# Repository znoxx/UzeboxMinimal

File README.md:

UzeboxMinimal
=============

Uzebox minimal design. The goal - to creat reprodusable modular design with minimal set of components.
Original project is located at http://uzebox.org

Update 16-Oct-2014 (2): Created simple MIDI expansion board. Never tested, since no MIDI devices owned :). See readme.txt inside midi subdir.
Actually project finalized.

Update 16-Oct-2014: Added video extension for AD725, same structure as in other projects (eagle,schematics,toner-transfer).
Also untested version removed.
Currently version is fully tested and confirmed working.

Update 13-Oct-2014: Added SD Card adapter.
eagle - To be opened with Eagle Cad 7.x.
schematics - Schematics, top jumpers and placement. Also an example of microSD adapter soldering. 
toner-transfer - Ready-to-print file for toner transfer. Have fun!
For best results:
Non-SDHC cards. In case using 2GB cards or bigger, create first partition about 256Mb. 
This is more, than enough for UzeBOX roms. 
Most important part partition should be FAT16 with 16K clusters.

Update 04-Oct-2014: This version is fixed somehow and soldered. Appears to be working.
Files (in mainboard dir):	
eagle - To be opened with Eagle Cad 7.x.
schematics - Schematics, top jumpers and placement
scart - connection via SCART
toner-transfer - Ready-to-print file for toner transfer. Have fun!

Update 01-Oct-2014: Current version is NOT tested in a "wild". Placed to share with forum members.
Files (not-tested dir):	
*.brd and *.sch - To be opened with Eagle Cad 7.x
schematics.pdf - Schematics
board-bottom.pdf - For toner transfer. Must be validated for correct size after/before print. Please check schematics/board layout for jumpers on top.

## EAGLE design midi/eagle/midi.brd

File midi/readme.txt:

This midi extension daughterboard was never tested in wild.
Double check schematics with F2 revision of original UzeBox at http://belogic.com/uzebox/downloads.htm before crafting.
Feel free to report any issues.

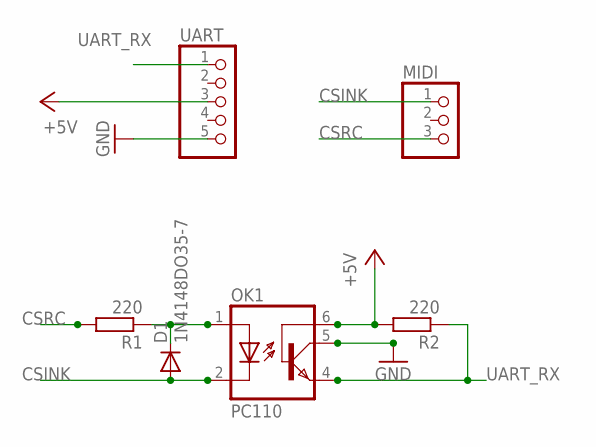
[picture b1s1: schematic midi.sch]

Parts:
D1: 1N4148DO35-7; DO35-7
MIDI: PINHD-1X3; 1X03
OK1: PC110; DIL06
R1, R2: 220; 0309V
UART: PINHD-1X5; 1X05

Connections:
+5V: OK1.6 (BAS), R2.2, UART.3
CSINK: D1.A, MIDI.1, OK1.2 (C)
CSRC: MIDI.3, R1.2
GND: OK1.5 (COL), UART.5
unnamed: D1.C, OK1.1 (A), R1.1
UART_RX: OK1.4 (EMI), R2.1, UART.1

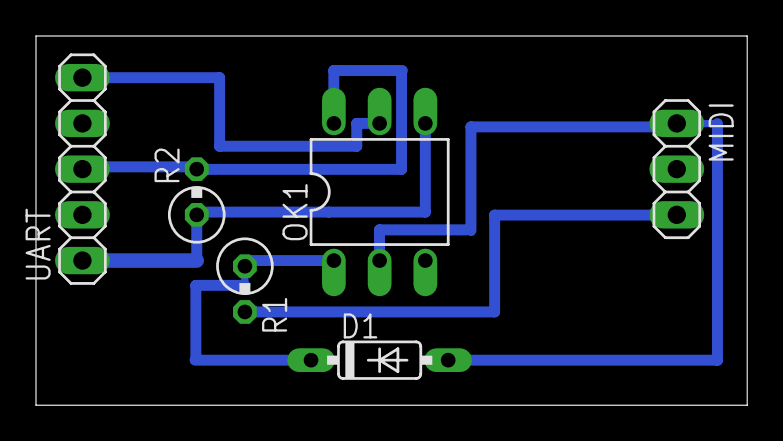
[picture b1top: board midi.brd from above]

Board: 2 copper layers, 39.5 x 20.5 mm, 6 parts (0 on the bottom side), 6 nets.

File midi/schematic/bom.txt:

Part	Value	Type
D1	1N4148	Diode DO35-7
"R1,R2"	220 Ohm	Resistor 0.125w
OK1	PC110	Optocoupler DIL06
UART 	x10 male pinhead	2.54 mm
MIDI	"x3 male pinhead, central connector cut"	2.54 mm

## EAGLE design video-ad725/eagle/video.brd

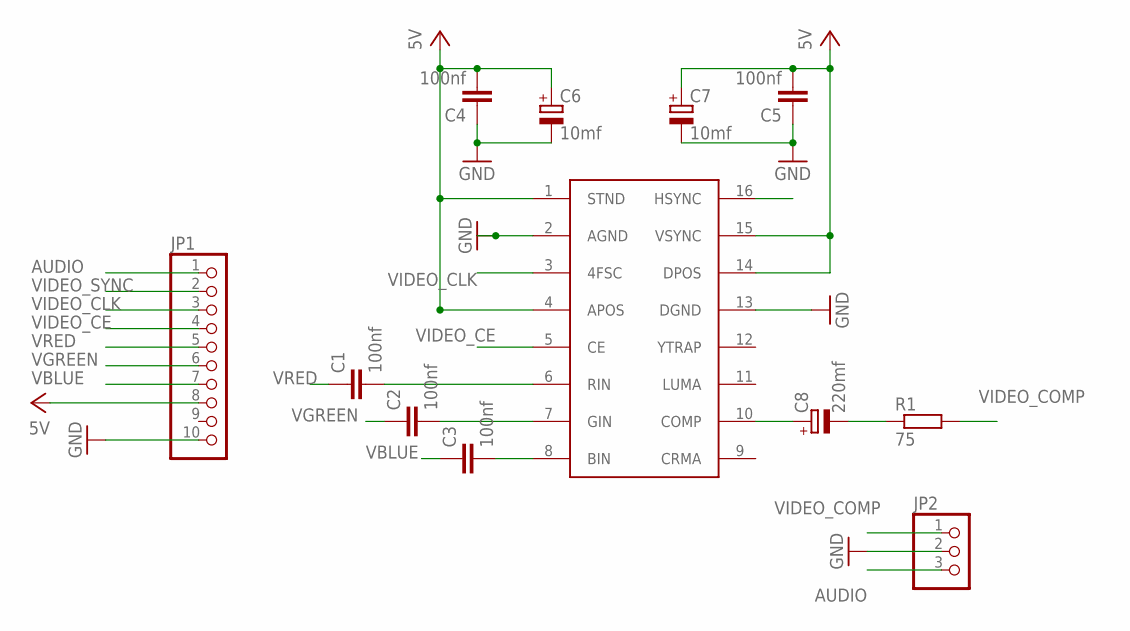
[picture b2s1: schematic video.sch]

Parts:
C1, C2, C3, C4, C5: 100nf; C0805
C6, C7: 10mf; E1,8-4
C8: 220mf; E1,8-4
JP1: PINHD-1X10; 1X10
JP2: PINHD-1X3; 1X03
R1: 75; R0805
U$1: AD725; SO16W

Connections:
AUDIO: JP1.1, JP2.3
GND: C4.1, C5.1, C6.-, C7.-, JP1.10, JP2.2, U$1.2 (AGND), U$1.13 (DGND)
unnamed: C1.2, U$1.6 (RIN)
unnamed: C2.2, U$1.7 (GIN)
unnamed: C3.2, U$1.8 (BIN)
unnamed: C8.+, U$1.10 (COMP)
unnamed: C8.-, R1.1
VBLUE: C3.1, JP1.7
VCC: C4.2, C5.2, C6.+, C7.+, JP1.8, U$1.1 (STND), U$1.4 (APOS), U$1.14 (DPOS), U$1.15 (VSYNC)
VGREEN: C2.1, JP1.6
VIDEO_CE: JP1.4, U$1.5 (CE)
VIDEO_CLK: JP1.3, U$1.3 (4FSC)
VIDEO_COMP: JP2.1, R1.2
VIDEO_SYNC: JP1.2, U$1.16 (HSYNC)
VRED: C1.1, JP1.5

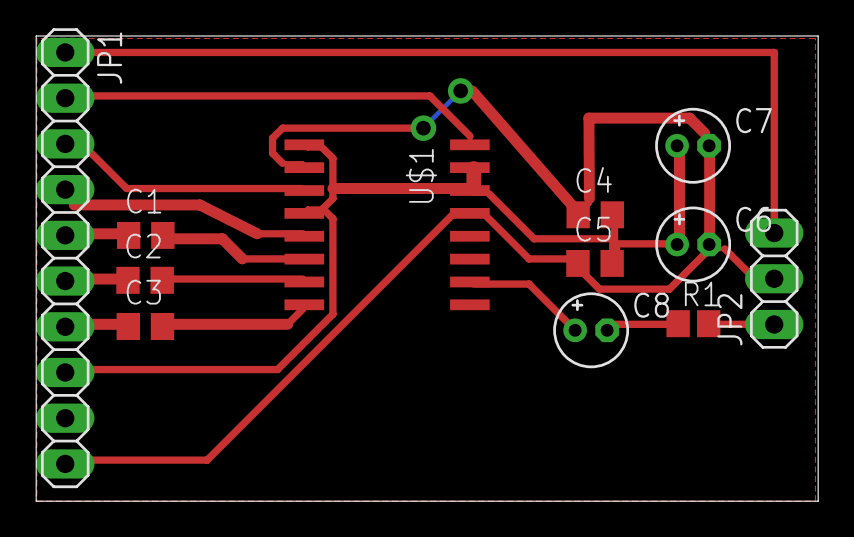
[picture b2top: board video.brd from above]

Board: 2 copper layers, 43.4 x 25.8 mm, 12 parts (0 on the bottom side), 15 nets.

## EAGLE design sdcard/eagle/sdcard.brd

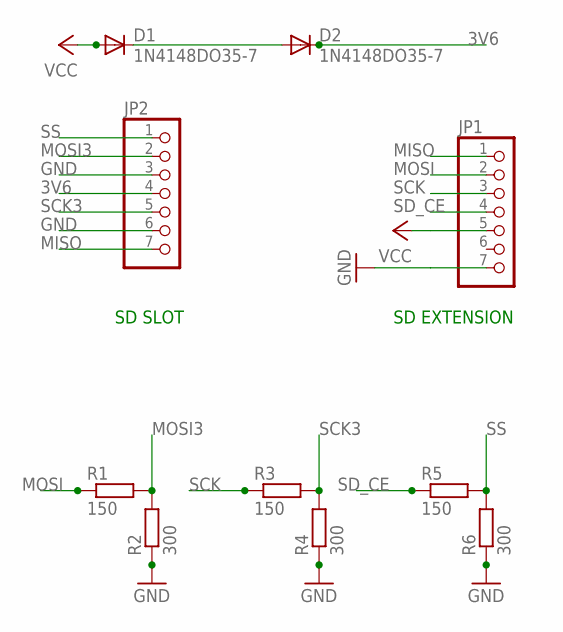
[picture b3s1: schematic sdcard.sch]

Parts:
D1, D2: 1N4148DO35-7; DO35-7
JP1, JP2: PINHD-1X7; 1X07
R1, R3, R5: 150; R0805
R2, R4, R6: 300; R0805

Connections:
3V6: D2.C, JP2.4
GND: JP1.7, JP2.3, JP2.6, R2.1, R4.1, R6.1
MISO: JP1.1, JP2.7
MOSI: JP1.2, R1.1
MOSI3: JP2.2, R1.2, R2.2
unnamed: D1.C, D2.A
SCK: JP1.3, R3.1
SCK3: JP2.5, R3.2, R4.2
SD_CE: JP1.4, R5.1
SS: JP2.1, R5.2, R6.2
VCC: D1.A, JP1.5

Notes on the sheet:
SD EXTENSION
SD SLOT

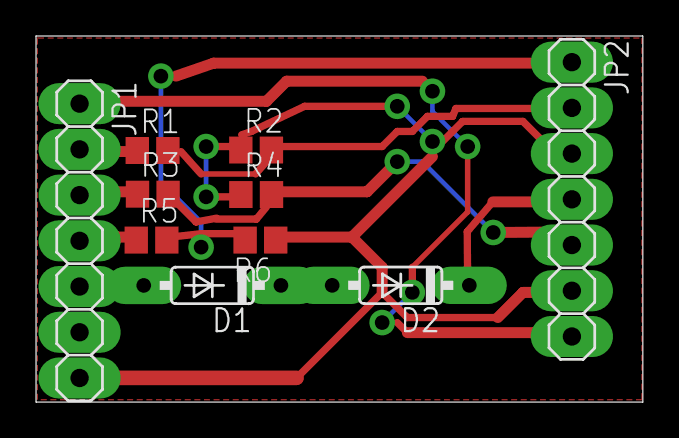
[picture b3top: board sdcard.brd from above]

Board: 2 copper layers, 33.7 x 20.3 mm, 10 parts (0 on the bottom side), 11 nets.

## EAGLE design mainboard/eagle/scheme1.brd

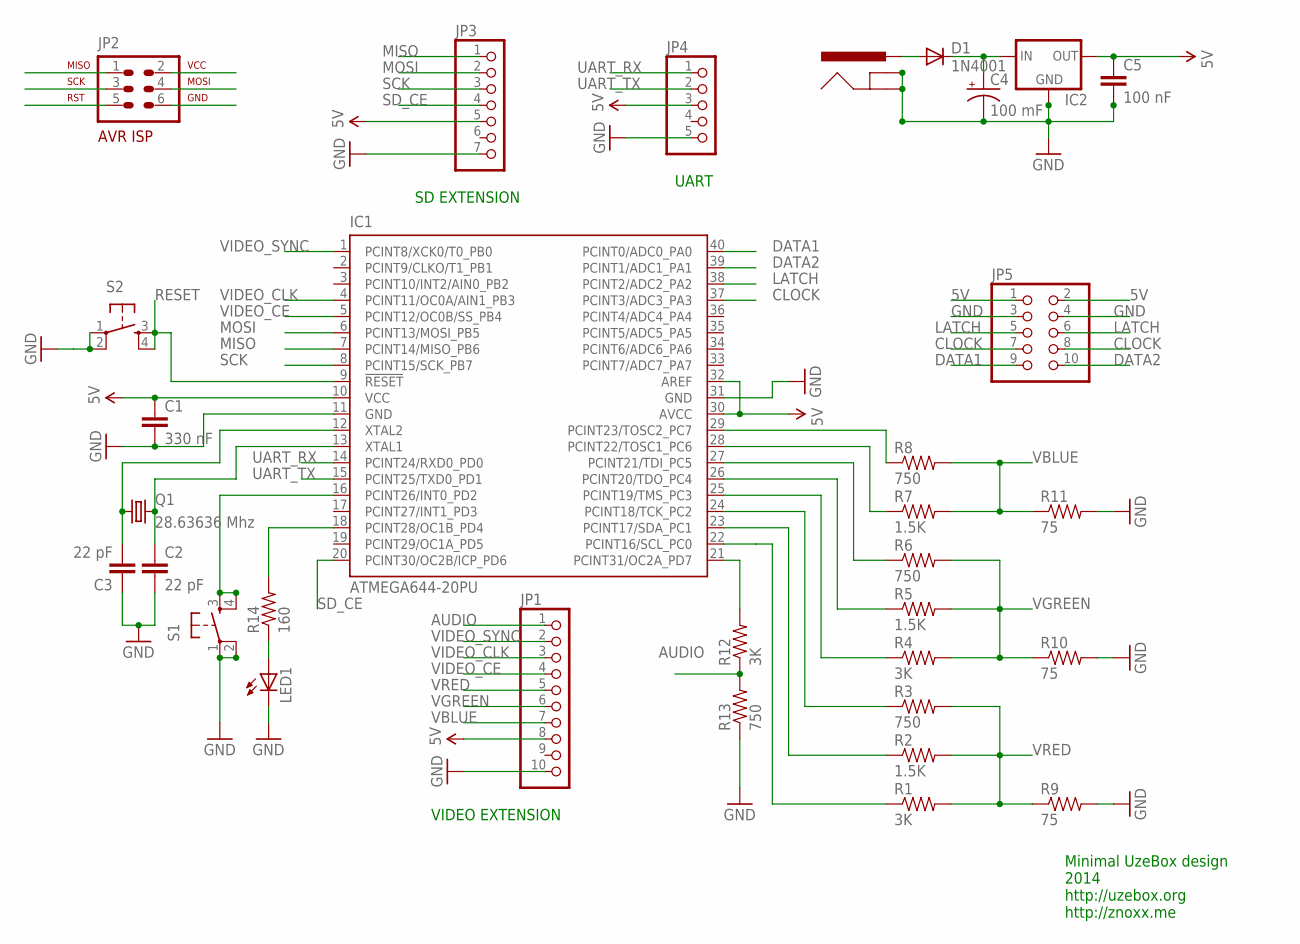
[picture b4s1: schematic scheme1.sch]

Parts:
C1: 330 nF; CAP-PTH-SMALL
C2, C3: 22 pF; CAP-PTH-SMALL
C4: 100 mF; CPOL-RADIAL-10UF-25V
C5: 100 nF; CAP-PTH-SMALL
D1: 1N4001; DIODE-1N4001
IC1: ATMEGA644-20PU; DIL40
IC2: V_REG_78XXSIDE; 78XXL
J1: POWER_JACKSLT; POWER_JACK_SLOT
JP1: PINHD-1X10; 1X10
JP2: AVR-ISP-6VERT; AVR-ISP-6
JP3: PINHD-1X7; 1X07
JP4: PINHD-1X5; 1X05
JP5: PINHD-2X5; 2X05
LED1: LED3MM
Q1: 28.63636 Mhz; HC49US
R1, R4, R12: 3K; AXIAL-0.3
R2, R5, R7: 1.5K; AXIAL-0.3
R3, R6, R8, R13: 750; AXIAL-0.3
R9, R10, R11: 75; AXIAL-0.3
R14: 160; AXIAL-0.3
S1, S2: TAC_SWITCHPTH; TACTILE-PTH

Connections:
5V: C1.1, C5.1, IC1.10 (VCC), IC1.30 (AVCC), IC1.32 (AREF), IC2.OUT, JP1.8, JP2.2, JP3.5, JP4.3, JP5.1, JP5.2
AUDIO: JP1.1, R12.P$1 (1), R13.P$2 (2)
CLOCK: IC1.37 (PCINT3/ADC3_PA3), JP5.7, JP5.8
DATA1: IC1.40 (PCINT0/ADC0_PA0), JP5.9
DATA2: IC1.39 (PCINT1/ADC1_PA1), JP5.10
GND: C1.2, C2.2, C3.1, C4.2 (-), C5.2, IC1.11 (GND), IC1.31 (GND), IC2.GND, J1.GND@1 (GNDBREAK), J1.GND@2 (GND), JP1.10, JP2.6, JP3.7, JP4.5, JP5.3, JP5.4, LED1.K (C), R9.P$2 (2), R10.P$2 (2), R11.P$2 (2), R13.P$1 (1), S1.1, S1.2, S2.1, S2.2
LATCH: IC1.38 (PCINT2/ADC2_PA2), JP5.5, JP5.6
MISO: IC1.7 (PCINT14/MISO_PB6), JP2.1, JP3.1
MOSI: IC1.6 (PCINT13/MOSI_PB5), JP2.4, JP3.2
unnamed: IC1.22 (PCINT16/SCL_PC0), R1.P$1 (1)
unnamed: IC1.23 (PCINT17/SDA_PC1), R2.P$1 (1)
unnamed: IC1.24 (PCINT18/TCK_PC2), R3.P$1 (1)
unnamed: C3.2, IC1.12 (XTAL2), Q1.1
unnamed: C2.1, IC1.13 (XTAL1), Q1.2
unnamed: IC1.25 (PCINT19/TMS_PC3), R4.P$1 (1)
unnamed: IC1.26 (PCINT20/TDO_PC4), R5.P$1 (1)
unnamed: IC1.27 (PCINT21/TDI_PC5), R6.P$1 (1)
unnamed: IC1.28 (PCINT22/TOSC1_PC6), R7.P$1 (1)
unnamed: IC1.29 (PCINT23/TOSC2_PC7), R8.P$1 (1)
unnamed: IC1.21 (PCINT31/OC2A_PD7), R12.P$2 (2)
unnamed: IC1.18 (PCINT28/OC1B_PD4), R14.P$2 (2)
unnamed: LED1.A, R14.P$1 (1)
unnamed: IC1.16 (PCINT26/INT0_PD2), S1.3, S1.4
unnamed: D1.A, J1.PWR
unnamed: C4.1 (+), D1.C, IC2.IN
RESET: IC1.9 (!RESET), JP2.5, S2.3, S2.4
SCK: IC1.8 (PCINT15/SCK_PB7), JP2.3, JP3.3
SD_CE: IC1.20 (PCINT30/OC2B/ICP_PD6), JP3.4
UART_RX: IC1.14 (PCINT24/RXD0_PD0), JP4.1
UART_TX: IC1.15 (PCINT25/TXD0_PD1), JP4.2
VBLUE: JP1.7, R7.P$2 (2), R8.P$2 (2), R11.P$1 (1)
VGREEN: JP1.6, R4.P$2 (2), R5.P$2 (2), R6.P$2 (2), R10.P$1 (1)
VIDEO_CE: IC1.5 (PCINT12/OC0B/SS_PB4), JP1.4
VIDEO_CLK: IC1.4 (PCINT11/OC0A/AIN1_PB3), JP1.3
VIDEO_SYNC: IC1.1 (PCINT8/XCK0/T0_PB0), JP1.2
VRED: JP1.5, R1.P$2 (2), R2.P$2 (2), R3.P$2 (2), R9.P$1 (1)

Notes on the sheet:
SD EXTENSION
UART
VIDEO EXTENSION
Minimal UzeBox design 2014 http://uzebox.org http://znoxx.me

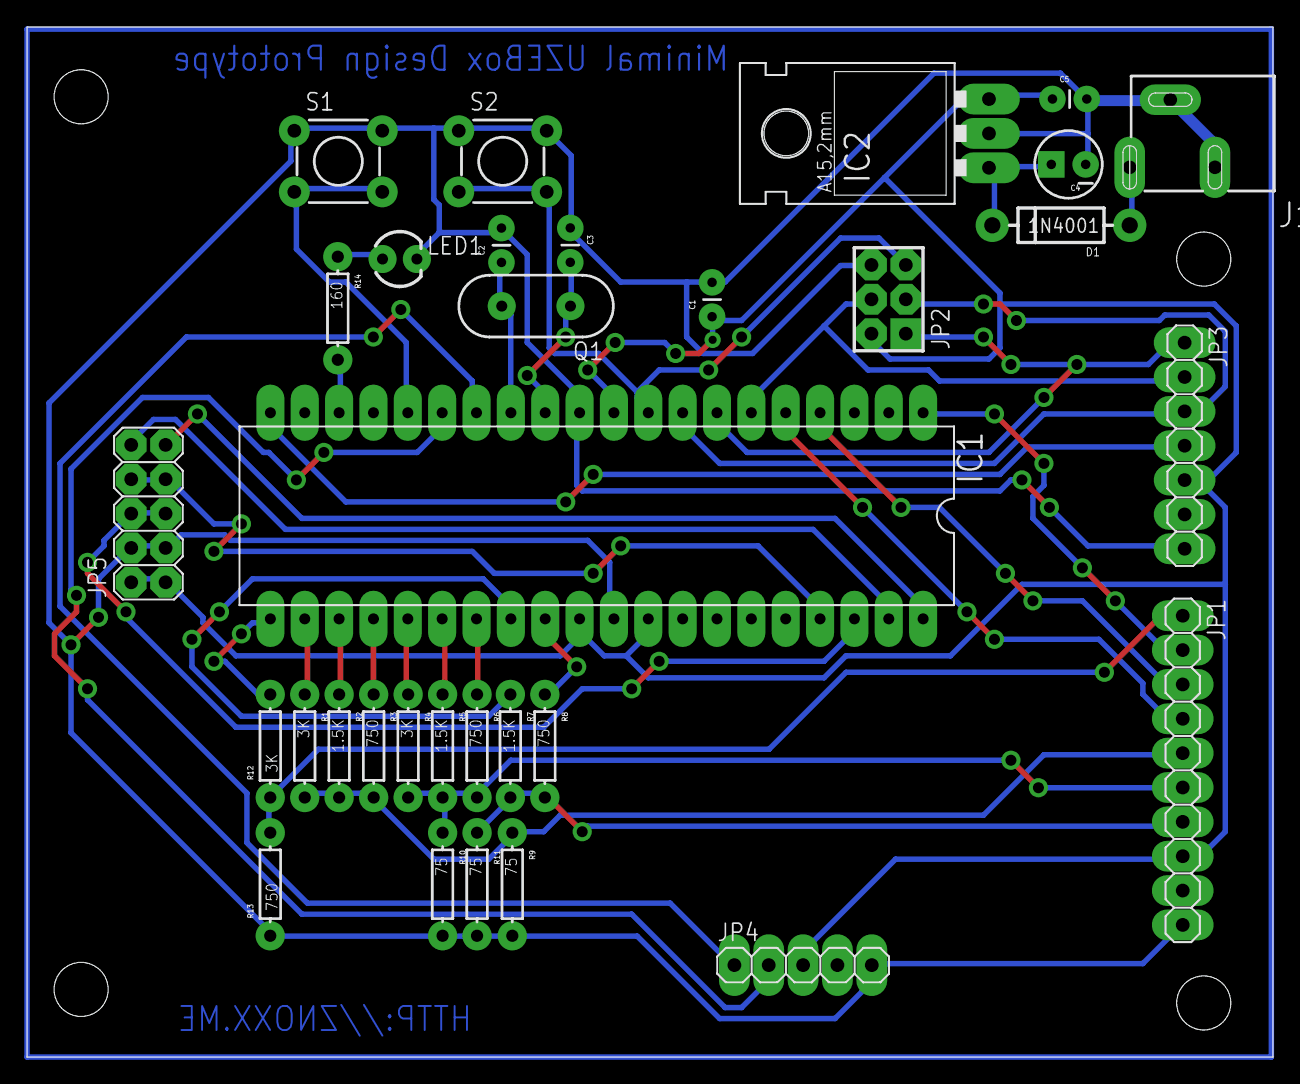
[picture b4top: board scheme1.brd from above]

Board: 2 copper layers, 92.1 x 76.2 mm, 32 parts (0 on the bottom side), 36 nets.

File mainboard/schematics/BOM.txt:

C1	Capacitor ceramic	330nf	1	
"C2,C3"	Capacitor ceramic	22pf	2	
C5	Capacitor ceramic	100nf	1	
C4	Capacitor electrolit	100mf	1	
IC1	ATMEGA644-20PU			
IC2	7805 Regulator		1	
"JP1,JP2,JP3,JP4,JP5"	PLS-40 connector		1	 cut it to pieces :)
LED1	LED	3mm	1	
Q1	Crystal	28.63636 Mhz	1	
D1	Diode	1N4001 	1	
J1	Powerjack			
"R1,R4,R12"	Resistor 0.125w	3K	4	
"R2,R5,R7"	Resistor 0.125w	1.5K	3	
"R3,R6,R8,R13"	Resistor 0.125w	750 Ohm	4	
R14	Resistor 0.125w	160 Ohm	1	
"R9,R10,R11"	Resistor 0.125w	75 Ohm	4	
"S1,S2"	Button		2

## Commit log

2014-10-01 First untested version
    Eagle schematics, toner transfer PDF and pdf schematics
2014-10-04 Fixed and validated version
2014-10-04 Added toner transfer stuff
2014-10-13 SD card adapter
    Checked version of SDCard adaptor. Includes example of connection of
    microSD-card adapter
2014-10-15 SD card adapter
    Small addendum to toner transfer part
2014-10-15 Added video extension board
    AD725 video extension, connected instead of SCART connector.
2014-10-16 MIDI extension board
    Added MIDI extension board, untested version.
2014-10-16 Some illustrations
    Added some photos to illustrate
2014-10-16 Some more pics

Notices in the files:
parts and their libraries:
SparkFun-Capacitors: Licensing: Creative Commons ShareAlike 4.0 International - https://creativecommons.org/licenses/by-sa/4.0
